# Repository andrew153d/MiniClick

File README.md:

# MiniClick
A small four way clickable joystick

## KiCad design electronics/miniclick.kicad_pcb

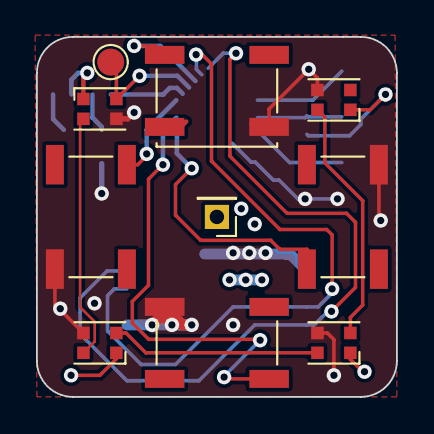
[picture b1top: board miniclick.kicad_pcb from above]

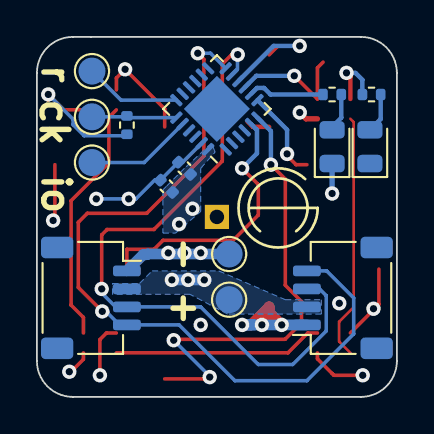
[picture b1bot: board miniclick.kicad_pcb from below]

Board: 4 copper layers, 20.0 x 20.0 mm, 25 parts (15 on the bottom side), 18 nets.

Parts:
C2: 4.7u; C_0402_1005Metric
C3: 100n; C_0402_1005Metric
D1, D6: LED; LED_0805_2012Metric
D2, D3, D4, D5: WS2812B; LED_WS2812B-2020_PLCC4_2.0x2.0mm
J1, J2: Stemma QT; JST_SH_SM04B-SRSS-TB_1x04-1MP_P1.00mm_Horizontal
J4: Joystick Mount; PinHeader_1x01_P2.00mm_Vertical
R1: locked; R_0402_1005Metric
R2: 1k; R_0402_1005Metric
R3: 10k; R_0402_1005Metric
SW1, SW2, SW3, SW5: SW_MEC_5E; EVQQ2B01W
TP1: nRST; TestPoint_Pad_D1.5mm
TP2: VCC; TestPoint_Pad_D1.5mm
TP3: GND; TestPoint_Pad_D1.5mm
TP4: SWDIO; TestPoint_Pad_D1.5mm
TP5: SWDCLK; TestPoint_Pad_D1.5mm
TP6: TestPoint; TestPoint_Pad_D1.5mm
U1: ATSAMD09D14A-M; QFN-24-1EP_4x4mm_P0.5mm_EP2.6x2.6mm

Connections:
+3.3V: C2.1, C3.1, D2.1 (VDD), D3.1 (VDD), D4.1 (VDD), D5.1 (VDD), J1.2, J2.2, R1.1, R2.1, TP2.1, U1.24 (VDD)
ADRS_LED: D2.4 (DIN), TP6.1, U1.9 (PA10)
GND: C2.2, C3.2, D1.1 (K), D2.3 (VSS), D3.3 (VSS), D4.3 (VSS), D5.3 (VSS), D6.1 (K), J1.1, J2.1, SW1.1, SW2.1, SW3.1, SW5.1, TP3.1, U1.23 (GND)
LED: R3.1, U1.8 (PA09)
unnamed: D1.2 (A), R1.2
unnamed: D2.2 (DOUT), D3.4 (DIN)
unnamed: D3.2 (DOUT), D4.4 (DIN)
unnamed: D4.2 (DOUT), D5.4 (DIN)
unnamed: D6.2 (A), R3.2
PA2: SW5.4 (A), U1.10 (PA11)
PA4: SW1.4 (A), U1.5 (PA06)
PA5: SW2.4 (A), U1.6 (PA07)
PA6: SW3.4 (A), U1.7 (PA08)
SCL: J1.4, J2.4, U1.12 (PA15)
SDA: J1.3, J2.3, U1.11 (PA14)
SWDCLK: R2.2, TP5.1, U1.19 (PA30/SWCLK)
SWDIO: TP4.1, U1.20 (PA31/SWDIO)
nRST: TP1.1, U1.18 (PA28/~RST)

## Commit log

2023-07-24 using adafruit Neopixel driver, doesnt work
2023-08-02 I2C not working
2023-08-03 working I2C discovery
2023-08-04 I2C working and reading buttons
2023-08-10 pcb ordered
2023-08-12 first ws2812 working
2023-08-12 working ws2812b driver
2023-08-28 pcb V2
